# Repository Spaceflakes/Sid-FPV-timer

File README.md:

# Sid-FPV-timer

An integrated, multi node FPV drone race timing and lap tracking system designed for competitive event management and RotorHazard compatibility.

---

## Overview

**Sid-FPV-timer** is an all in one hardware timing platform engineered for competitive FPV drone racing. By integrating multi channel RF receivers, dedicated timing control, robust power regulation, and host compute docking onto a single unified board, it simplifies trackside setup and eliminates complex external wiring harnesses.

---

## Highlights

- **Multi-Node RF Tracking:** Onboard receiver array designed for multi pilot simultaneous race tracking and real time signal analysis.
- **Host Compute Docking:** Direct interface for an onboard single board computer running race timing management software.
- **Dedicated Timing Architecture:** Dedicated microcontrollers handling high-resolution lap detection, wireless connectivity, and telemetry.
- **Wide-Input Power Regulation:** High efficiency power delivery and protection circuitry designed for field battery operation.
- **Peripherals & Thermal Management:** Headers and drivers for active cooling fans, audio/visual cues, and user inputs.

---

## Inspiration & Acknowledgements

This project draws strong inspiration from the pioneering work of **[NuclearQuads](https://nuclearquads.com)** and their **NuclearHazard** timer series. Made for the open-source [RotorHazard](https://github.com/RotorHazard/RotorHazard) ecosystem.

---

## Project Structure

```text
Sid-FPV-timer/
├── PCB/                     # KiCad hardware design files
│   ├── production/          # Ready to order Gerber archives and SMT files
│   └── ...                  # Schematic sheets, board layout, and libraries
├── img/                     # 3D hardware renders & media assets
├── LICENSE                  # GNU AGPL-3.0
└── README.md
```

---

## Status

> This project is currently in active hardware prototyping and validation. Detailed documentation, firmware setups, and assembly instructions will be expanded as revisions progress.

---

## Designer

- **Designer:** Siddesh Jain ([Hex Aerospace](https://hexaerospace.in))

---

## License

This project is licensed under the **GNU Affero General Public License v3.0 (AGPL-3.0)**. See the [LICENSE](LICENSE) file for details.

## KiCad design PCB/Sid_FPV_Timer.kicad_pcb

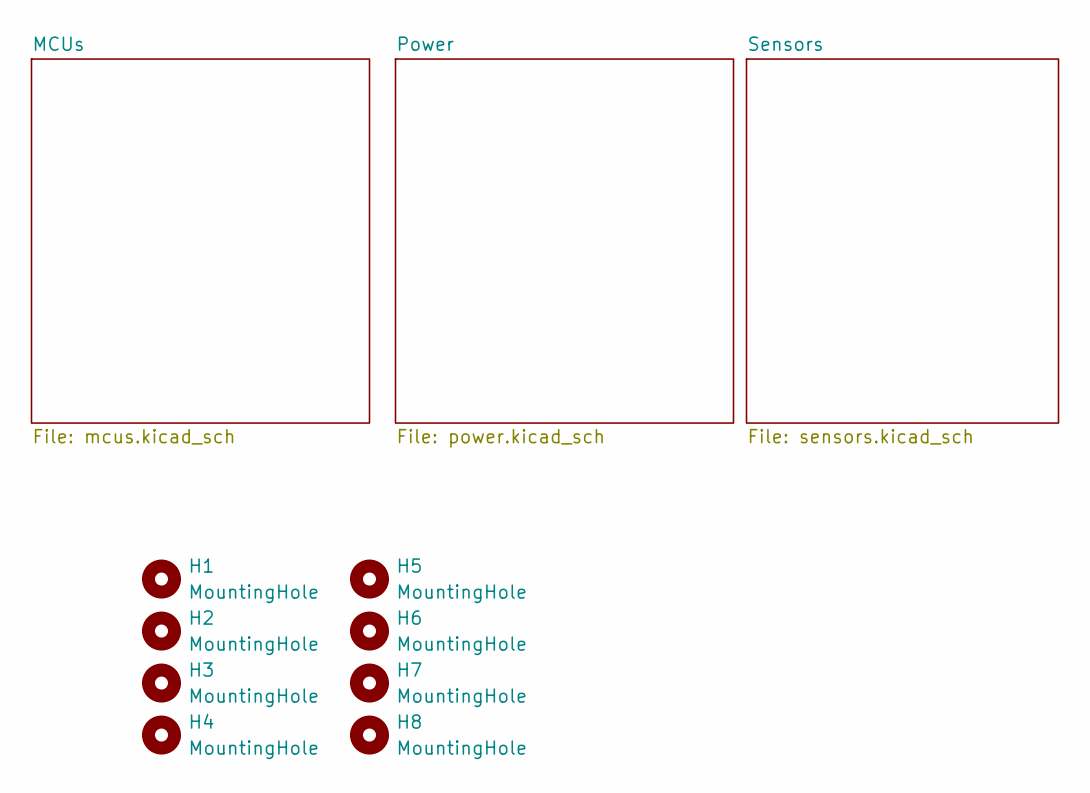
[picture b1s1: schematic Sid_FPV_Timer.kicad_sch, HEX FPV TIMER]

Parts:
H1, H2, H3, H4: MountingHole; MountingHole_2.7mm_M2.5_Pad_Via
H5, H6, H7, H8: MountingHole; MountingHole_3.2mm_M3_Pad_Via

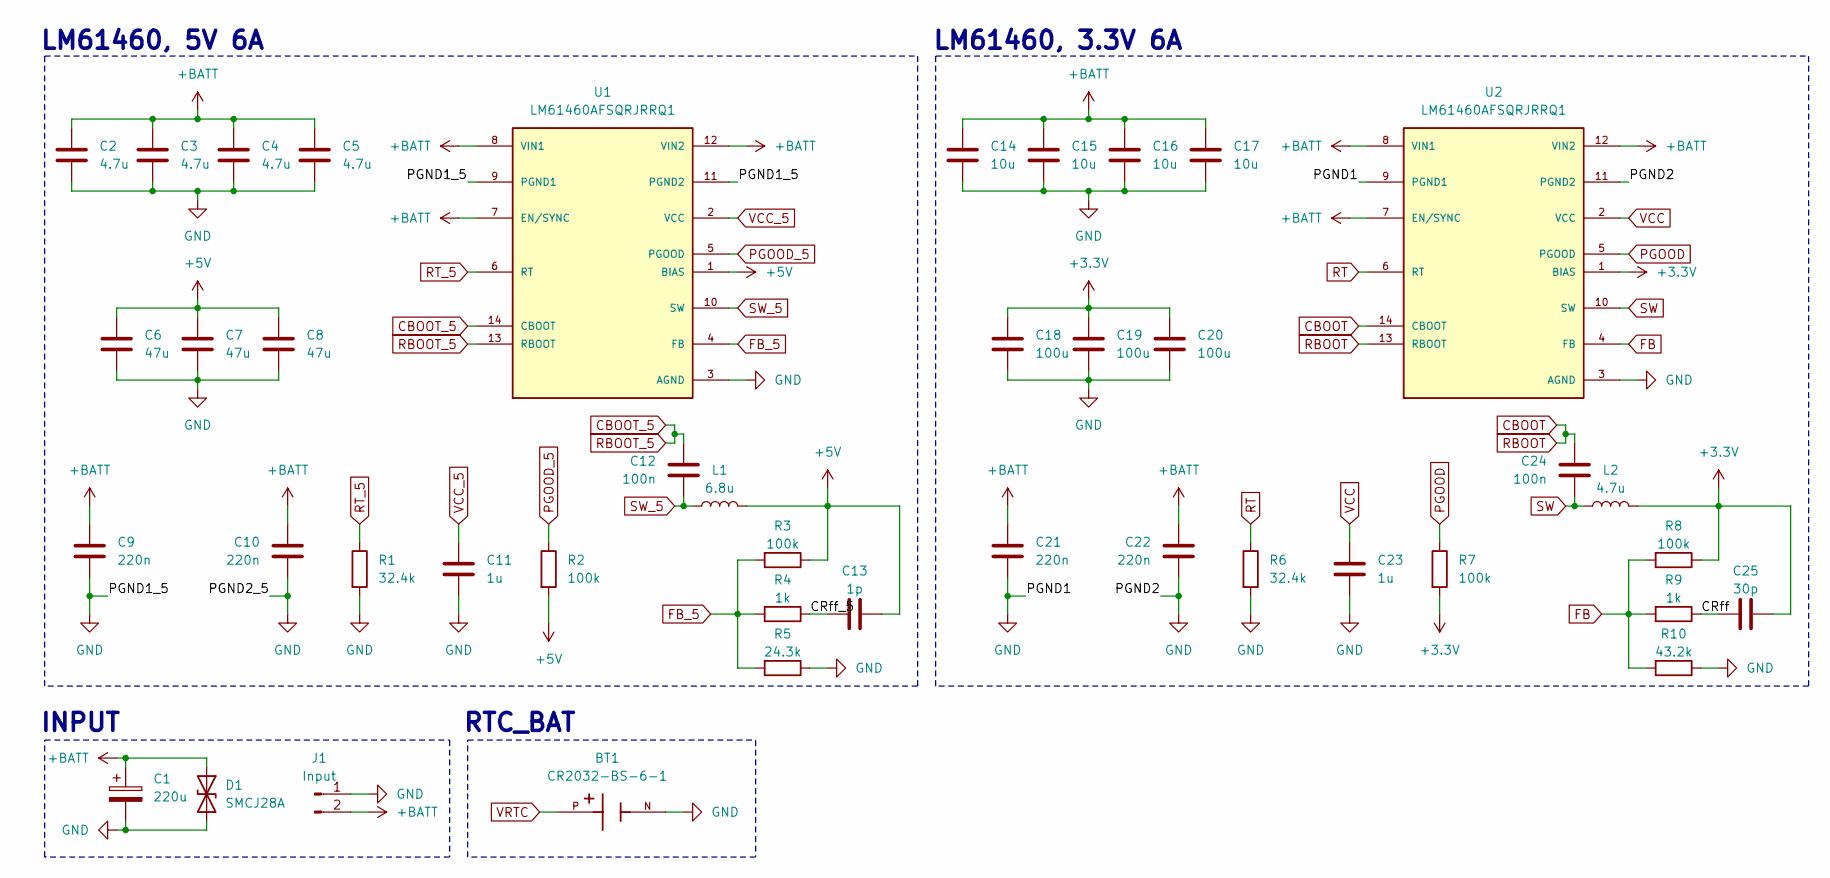
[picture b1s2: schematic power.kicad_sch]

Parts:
BT1: CR2032-BS-6-1; BatteryHolder_Keystone_1060_1x2032; MPN CR2032-BS-6-1; LCSC C964758
C1: 220u; CP_Elec_10x10; LCSC C2887271
C2, C3, C4, C5: 4.7u; C_0805_2012Metric; LCSC C98192
C6, C7, C8: 47u; C_0603_1608Metric; LCSC C730416
C9, C10, C21, C22: 220n; C_0603_1608Metric; LCSC C64705
C11, C23: 1u; C_0603_1608Metric; LCSC C15849
C12, C24: 100n; C_0603_1608Metric; LCSC C1591
C13: 1p; C_0603_1608Metric; LCSC C5137611
C14, C15, C16, C17: 10u; C_0805_2012Metric; LCSC C440198
C18, C19, C20: 100u; C_0805_2012Metric; LCSC C141660
C25: 30p; C_0603_1608Metric; LCSC C113797
D1: SMCJ28A; D_SMC; LCSC C42371538
J1: Input; AMASS_XT60PW-M_1x02_P7.20mm_Horizontal; LCSC C98732
L1: 6.8u; L_7.3x7.3_H3.5; LCSC C41415571
L2: 4.7u; L_7.3x7.3_H3.5; LCSC C167220
R1, R6: 32.4k; R_0603_1608Metric; LCSC C2982943
R2, R3, R7, R8: 100k; R_0603_1608Metric; LCSC C122538
R4, R9: 1k; R_0603_1608Metric; LCSC C118155
R5: 24.3k; R_0603_1608Metric; LCSC C403097
R10: 43.2k; R_0603_1608Metric; LCSC C2930102
U1, U2: LM61460AFSQRJRRQ1; IC_LM61460AFSQRJRRQ1; PARTREV D; LCSC C2864505

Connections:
+5V: C6.1, C7.1, C8.1, C13.2, L1.2, R2.2, R3.1, U1.1 (BIAS); also elsewhere on the board
+BATT: C1.1, C2.1, C3.1, C4.1, C5.1, C9.1, C10.1, C14.1, C15.1, C16.1, C17.1, C21.1, C22.1, D1.1 (A1), J1.2, U1.7 (EN/SYNC), U1.8 (VIN1), U1.12 (VIN2), U2.7 (EN/SYNC), U2.8 (VIN1), U2.12 (VIN2); also elsewhere on the board
/Power/CRff: C25.1, R9.1
/Power/CRff_5: C13.1, R4.1
CBOOT: C24.2, U2.13 (RBOOT), U2.14 (CBOOT)
CBOOT_5: C12.2, U1.13 (RBOOT), U1.14 (CBOOT)
FB: R8.2, R9.2, R10.2, U2.4 (FB)
FB_5: R3.2, R4.2, R5.2, U1.4 (FB)
GND: BT1.N, C1.2, C2.2, C3.2, C4.2, C5.2, C6.2, C7.2, C8.2, C9.2, C10.2, C11.2, C14.2, C15.2, C16.2, C17.2, C18.2, C19.2, C20.2, C21.2, C22.2, C23.2, D1.2 (A2), J1.1, R1.2, R5.1, R6.2, R10.1, U1.3 (AGND), U1.9 (PGND1), U1.11 (PGND2), U2.3 (AGND), U2.9 (PGND1), U2.11 (PGND2); also elsewhere on the board
PGOOD: R7.1, U2.5 (PGOOD)
PGOOD_5: R2.1, U1.5 (PGOOD)
RT: R6.1, U2.6 (RT)
RT_5: R1.1, U1.6 (RT)
SW: C24.1, L2.1, U2.10 (SW)
SW_5: C12.1, L1.1, U1.10 (SW)
VCC: C23.1, U2.2 (VCC)
VCC_5: C11.1, U1.2 (VCC)
VDD: C18.1, C19.1, C20.1, C25.2, L2.2, R7.2, R8.1, U2.1 (BIAS); also elsewhere on the board
VRTC: BT1.P; also elsewhere on the board

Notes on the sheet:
LM61460, 5V 6A
LM61460, 3.3V 6A
RTC_BAT
INPUT

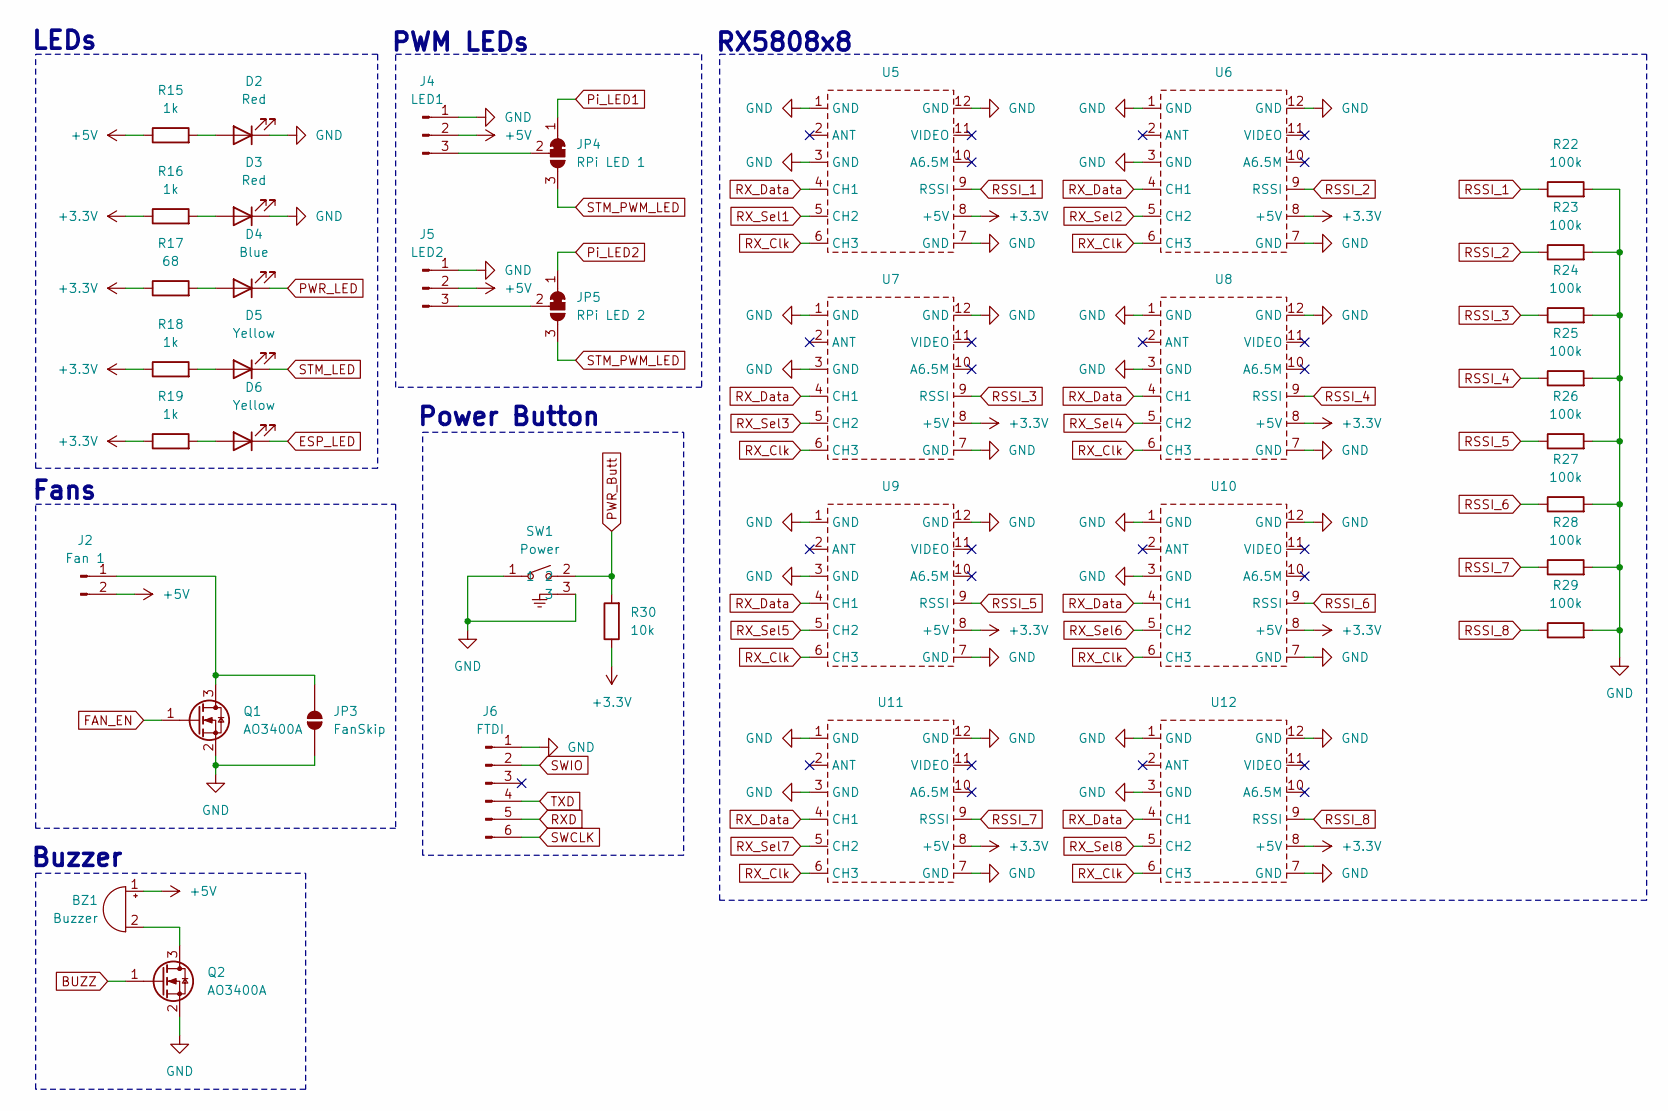
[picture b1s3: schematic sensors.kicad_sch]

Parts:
BZ1: Buzzer; Buzzer 9650Y; LCSC C96127
D2, D3: Red; LED_0805_2012Metric; LCSC C965812
D4: Blue; LED_0603_1608Metric; LCSC C46610608
D5, D6: Yellow; LED_0805_2012Metric; LCSC C965814
J2: Fan 1; JST_XA_B02B-XASK-1_1x02_P2.50mm_Vertical; LCSC C158012
J4: LED1; JST_XH_B3B-XH-A_1x03_P2.50mm_Vertical; LCSC C144394
J5: LED2; JST_XH_B3B-XH-A_1x03_P2.50mm_Vertical; LCSC C144394
J6: FTDI; PinHeader_1x06_P2.54mm_Vertical
JP3: FanSkip; SolderJumper-2_P1.3mm_Open_RoundedPad1.0x1.5mm
JP4: RPi LED 1; SolderJumper-3_P1.3mm_Bridged12_RoundedPad1.0x1.5mm
JP5: RPi LED 2; SolderJumper-3_P1.3mm_Bridged12_RoundedPad1.0x1.5mm
Q1, Q2: AO3400A; SOT-23; LCSC C20917
R15, R16, R18, R19: 1k; R_0603_1608Metric; LCSC C118155
R17: 68; R_0603_1608Metric; LCSC C27592
R22, R23, R24, R25, R26, R27, R28, R29: 100k; R_0603_1608Metric; LCSC C122538
R30: 10k; R_0603_1608Metric; LCSC C191124
SW1: Power; SW-TH_G-SWITCH_GT-TCB73B-H048-L1; LCSC C2890354
U5, U6, U7, U8, U9, U10, U11, U12: RX5808_Module

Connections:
+5V: BZ1.1 (+), J2.2, J4.2, J5.2, R15.1; also elsewhere on the board
BUZZ: Q2.1 (G); also elsewhere on the board
ESP_LED: D6.1 (K); also elsewhere on the board
FAN_EN: Q1.1 (G); also elsewhere on the board
GND: D2.1 (K), D3.1 (K), J4.1, J5.1, J6.1, JP3.1 (A), Q1.2 (S), Q2.2 (S), R22.2, R23.2, R24.2, R25.2, R26.2, R27.2, R28.2, R29.2, SW1.1, SW1.3, U5.1 (GND), U5.3 (GND), U5.7 (GND), U5.12 (GND), U6.1 (GND), U6.3 (GND), U6.7 (GND), U6.12 (GND), U7.1 (GND), U7.3 (GND), U7.7 (GND), U7.12 (GND), U8.1 (GND), U8.3 (GND), U8.7 (GND), U8.12 (GND), U9.1 (GND), U9.3 (GND), U9.7 (GND), U9.12 (GND), U10.1 (GND), U10.3 (GND), U10.7 (GND), U10.12 (GND), U11.1 (GND), U11.3 (GND), U11.7 (GND), U11.12 (GND), U12.1 (GND), U12.3 (GND), U12.7 (GND), U12.12 (GND); also elsewhere on the board
unnamed: BZ1.2 (-), Q2.3 (D)
unnamed: D2.2 (A), R15.2
unnamed: D3.2 (A), R16.2
unnamed: D4.2 (A), R17.2
unnamed: D5.2 (A), R18.2
unnamed: D6.2 (A), R19.2
unnamed: J2.1, JP3.2 (B), Q1.3 (D)
unnamed: J4.3, JP4.2 (C)
unnamed: J5.3, JP5.2 (C)
PWR_Butt: R30.2, SW1.2; also elsewhere on the board
PWR_LED: D4.1 (K); also elsewhere on the board
Pi_LED1: JP4.1 (A); also elsewhere on the board
Pi_LED2: JP5.1 (A); also elsewhere on the board
RSSI_1: R22.1, U5.9 (RSSI); also elsewhere on the board
RSSI_2: R23.1, U6.9 (RSSI); also elsewhere on the board
RSSI_3: R24.1, U7.9 (RSSI); also elsewhere on the board
RSSI_4: R25.1, U8.9 (RSSI); also elsewhere on the board
RSSI_5: R26.1, U9.9 (RSSI); also elsewhere on the board
RSSI_6: R27.1, U10.9 (RSSI); also elsewhere on the board
RSSI_7: R28.1, U11.9 (RSSI); also elsewhere on the board
RSSI_8: R29.1, U12.9 (RSSI); also elsewhere on the board
RXD: J6.5; also elsewhere on the board
RX_Clk: U5.6 (CH3), U6.6 (CH3), U7.6 (CH3), U8.6 (CH3), U9.6 (CH3), U10.6 (CH3), U11.6 (CH3), U12.6 (CH3); also elsewhere on the board
RX_Data: U5.4 (CH1), U6.4 (CH1), U7.4 (CH1), U8.4 (CH1), U9.4 (CH1), U10.4 (CH1), U11.4 (CH1), U12.4 (CH1); also elsewhere on the board
RX_Sel1: U5.5 (CH2); also elsewhere on the board
RX_Sel2: U6.5 (CH2); also elsewhere on the board
RX_Sel3: U7.5 (CH2); also elsewhere on the board
RX_Sel4: U8.5 (CH2); also elsewhere on the board
RX_Sel5: U9.5 (CH2); also elsewhere on the board
RX_Sel6: U10.5 (CH2); also elsewhere on the board
RX_Sel7: U11.5 (CH2); also elsewhere on the board
RX_Sel8: U12.5 (CH2); also elsewhere on the board
STM_LED: D5.1 (K); also elsewhere on the board
STM_PWM_LED: JP4.3 (B), JP5.3 (B); also elsewhere on the board
SWCLK: J6.6; also elsewhere on the board
SWIO: J6.2; also elsewhere on the board
TXD: J6.4; also elsewhere on the board
VDD: R16.1, R17.1, R18.1, R19.1, R30.1, U5.8 (+5V), U6.8 (+5V), U7.8 (+5V), U8.8 (+5V), U9.8 (+5V), U10.8 (+5V), U11.8 (+5V), U12.8 (+5V); also elsewhere on the board

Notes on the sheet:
Power Button
PWM LEDs
Buzzer
RX5808x8
Fans
LEDs

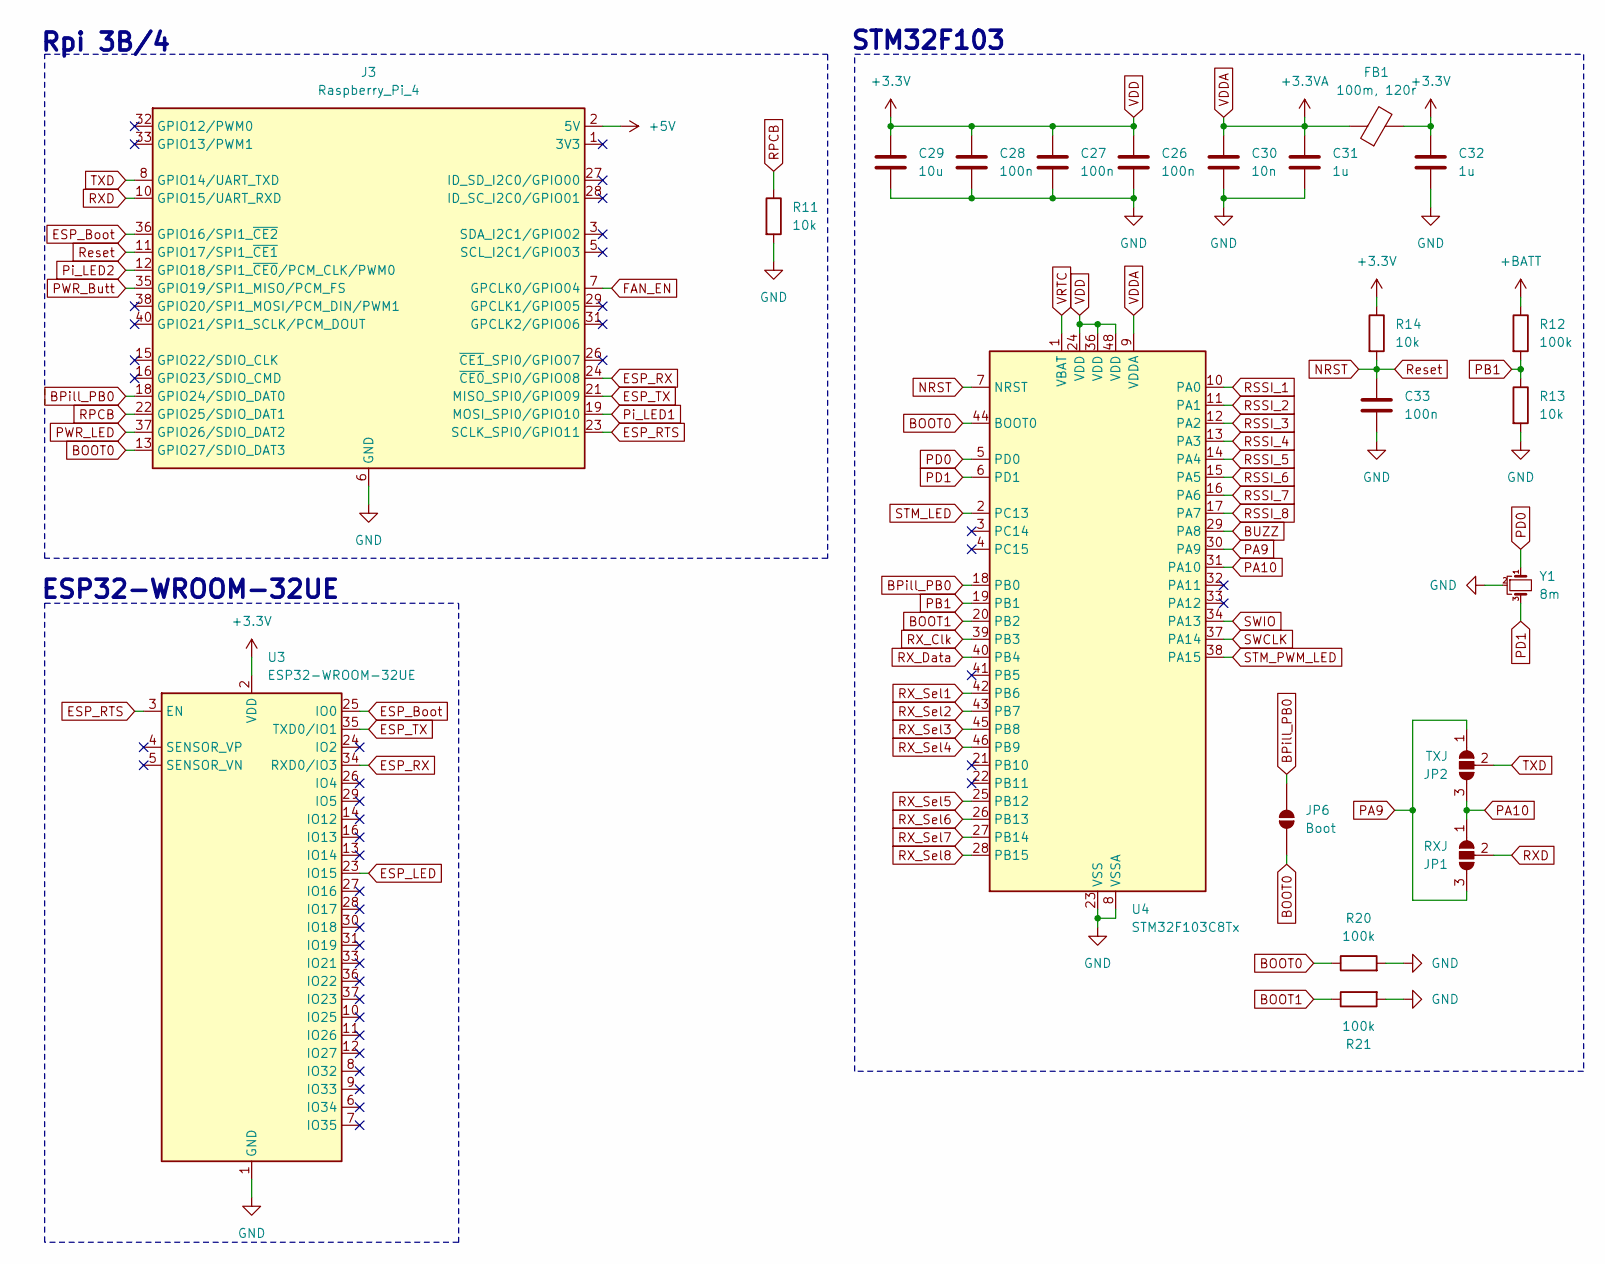
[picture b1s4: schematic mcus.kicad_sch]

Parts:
C26, C27, C28, C33: 100n; C_0603_1608Metric; LCSC C1591
C29: 10u; C_0603_1608Metric; LCSC C92487
C30: 10n; C_0603_1608Metric; LCSC C100042
C31, C32: 1u; C_0603_1608Metric; LCSC C15849
FB1: 100m, 120r; C_0603_1608Metric; LCSC C76893
J3: Raspberry_Pi_4; PinSocket_2x20_P2.54mm_Vertical; LCSC C2977589
JP1: RXJ; SolderJumper-3_P1.3mm_Open_RoundedPad1.0x1.5mm_NumberLabels
JP2: TXJ; SolderJumper-3_P1.3mm_Open_RoundedPad1.0x1.5mm_NumberLabels
JP6: Boot; SolderJumper-2_P1.3mm_Open_RoundedPad1.0x1.5mm
R11, R13, R14: 10k; R_0603_1608Metric; LCSC C191124
R12, R20, R21: 100k; R_0603_1608Metric; LCSC C122538
U3: ESP32-WROOM-32UE; LCSC C701346
U4: STM32F103C8Tx; LQFP-48_7x7mm_P0.5mm; LCSC C8734
Y1: 8m; Resonator_SMD_Murata_CSTxExxV-3Pin_3.0x1.1mm; LCSC C22549

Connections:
+5V: J3.2 (5V), J3.4 (5V); also elsewhere on the board
+BATT: R12.1; also elsewhere on the board
BOOT0: J3.13 (GPIO27/SDIO_DAT3), JP6.1 (A), R20.1, U4.44 (BOOT0)
BOOT1: R21.1, U4.20 (PB2)
BPill_PB0: J3.18 (GPIO24/SDIO_DAT0), JP6.2 (B), U4.18 (PB0)
BUZZ: U4.29 (PA8); also elsewhere on the board
ESP_Boot: J3.36 (GPIO16/SPI1_~CE2), U3.25 (IO0)
ESP_LED: U3.23 (IO15); also elsewhere on the board
ESP_RTS: J3.23 (SCLK_SPI0/GPIO11), U3.3 (EN)
ESP_RX: J3.24 (~CE0_SPI0/GPIO08), U3.34 (RXD0/IO3)
ESP_TX: J3.21 (MISO_SPI0/GPIO09), U3.35 (TXD0/IO1)
FAN_EN: J3.7 (GPCLK0/GPIO04); also elsewhere on the board
GND: C26.2, C27.2, C28.2, C29.2, C30.2, C31.2, C32.2, C33.2, J3.6 (GND), J3.9 (GND), J3.14 (GND), J3.20 (GND), J3.25 (GND), J3.30 (GND), J3.34 (GND), J3.39 (GND), R11.2, R13.2, R20.2, R21.2, U3.1 (GND), U3.15 (GND), U3.38 (GND), U3.39 (GND), U4.8 (VSSA), U4.23 (VSS), U4.35 (VSS), U4.47 (VSS), Y1.2; also elsewhere on the board
NRST: C33.1, J3.11 (GPIO17/SPI1_~CE1), R14.2, U4.7 (NRST)
PA9: JP1.3 (B), JP2.1 (A), U4.30 (PA9)
PA10: JP1.1 (A), JP2.3 (B), U4.31 (PA10)
PB1: R12.2, R13.1, U4.19 (PB1)
PD0: U4.5 (PD0), Y1.1
PD1: U4.6 (PD1), Y1.3
PWR_Butt: J3.35 (GPIO19/SPI1_MISO/PCM_FS); also elsewhere on the board
PWR_LED: J3.37 (GPIO26/SDIO_DAT2); also elsewhere on the board
Pi_LED1: J3.19 (MOSI_SPI0/GPIO10); also elsewhere on the board
Pi_LED2: J3.12 (GPIO18/SPI1_~CE0/PCM_CLK/PWM0); also elsewhere on the board
RPCB: J3.22 (GPIO25/SDIO_DAT1), R11.1
RSSI_1: U4.10 (PA0); also elsewhere on the board
RSSI_2: U4.11 (PA1); also elsewhere on the board
RSSI_3: U4.12 (PA2); also elsewhere on the board
RSSI_4: U4.13 (PA3); also elsewhere on the board
RSSI_5: U4.14 (PA4); also elsewhere on the board
RSSI_6: U4.15 (PA5); also elsewhere on the board
RSSI_7: U4.16 (PA6); also elsewhere on the board
RSSI_8: U4.17 (PA7); also elsewhere on the board
RXD: J3.10 (GPIO15/UART_RXD), JP1.2 (C); also elsewhere on the board
RX_Clk: U4.39 (PB3); also elsewhere on the board
RX_Data: U4.40 (PB4); also elsewhere on the board
RX_Sel1: U4.42 (PB6); also elsewhere on the board
RX_Sel2: U4.43 (PB7); also elsewhere on the board
RX_Sel3: U4.45 (PB8); also elsewhere on the board
RX_Sel4: U4.46 (PB9); also elsewhere on the board
RX_Sel5: U4.25 (PB12); also elsewhere on the board
RX_Sel6: U4.26 (PB13); also elsewhere on the board
RX_Sel7: U4.27 (PB14); also elsewhere on the board
RX_Sel8: U4.28 (PB15); also elsewhere on the board
STM_LED: U4.2 (PC13); also elsewhere on the board
STM_PWM_LED: U4.38 (PA15); also elsewhere on the board
SWCLK: U4.37 (PA14); also elsewhere on the board
SWIO: U4.34 (PA13); also elsewhere on the board
TXD: J3.8 (GPIO14/UART_TXD), JP2.2 (C); also elsewhere on the board
VDD: C26.1, C27.1, C28.1, C29.1, C32.1, FB1.2, R14.1, U3.2 (VDD), U4.24 (VDD), U4.36 (VDD), U4.48 (VDD); also elsewhere on the board
VDDA: C30.1, C31.1, FB1.1, U4.9 (VDDA)
VRTC: U4.1 (VBAT); also elsewhere on the board

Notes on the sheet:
ESP32-WROOM-32UE
Rpi 3B/4
STM32F103

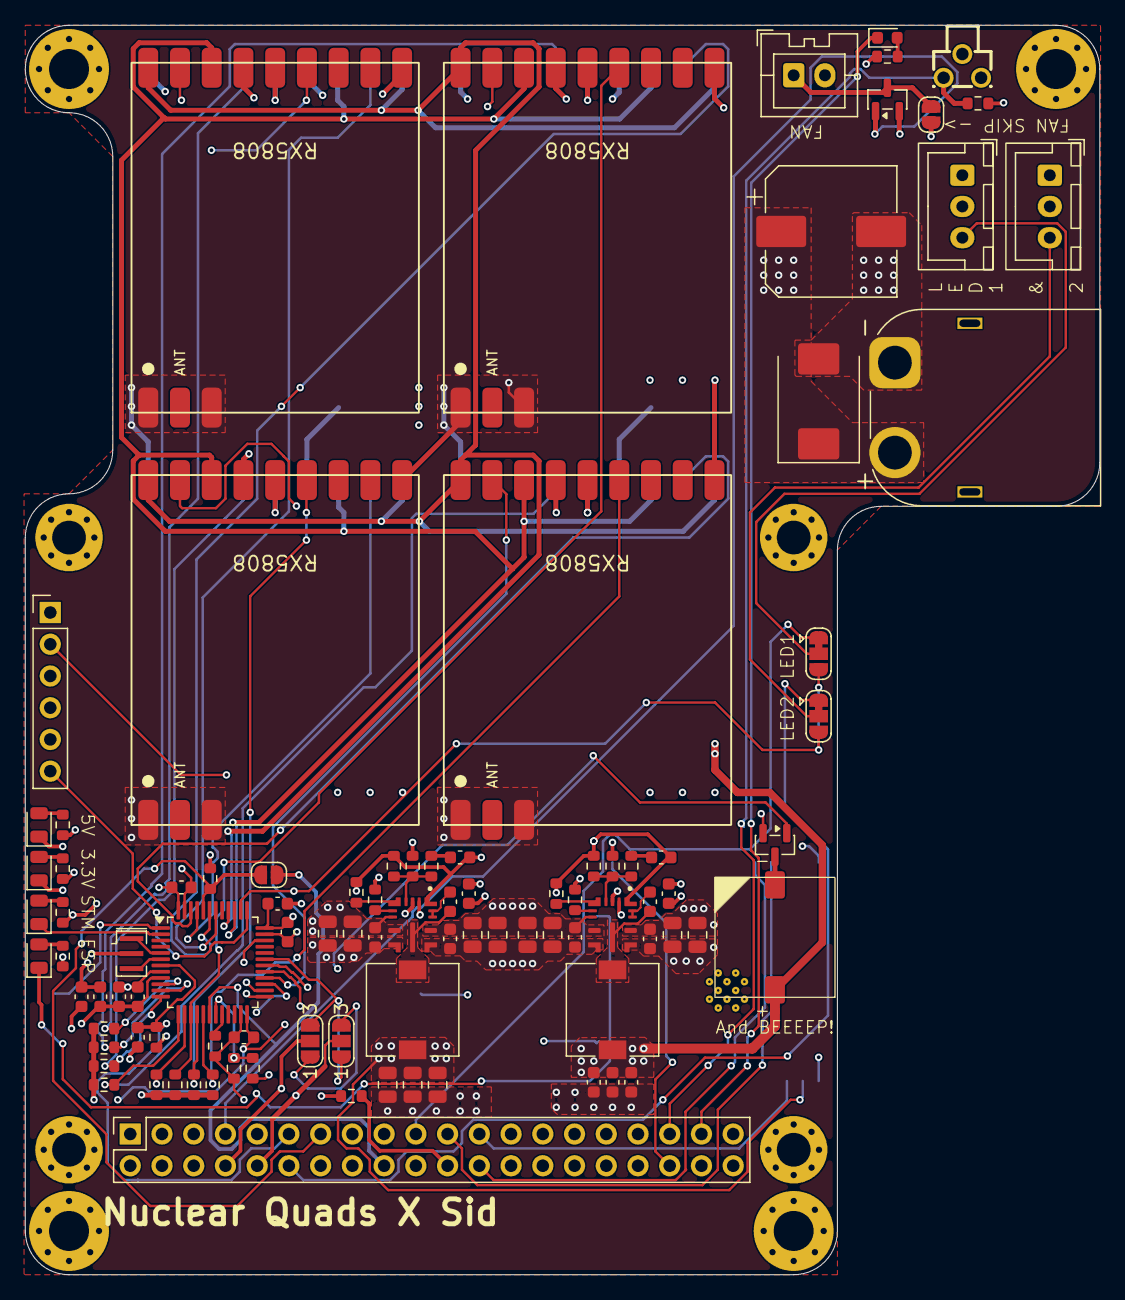
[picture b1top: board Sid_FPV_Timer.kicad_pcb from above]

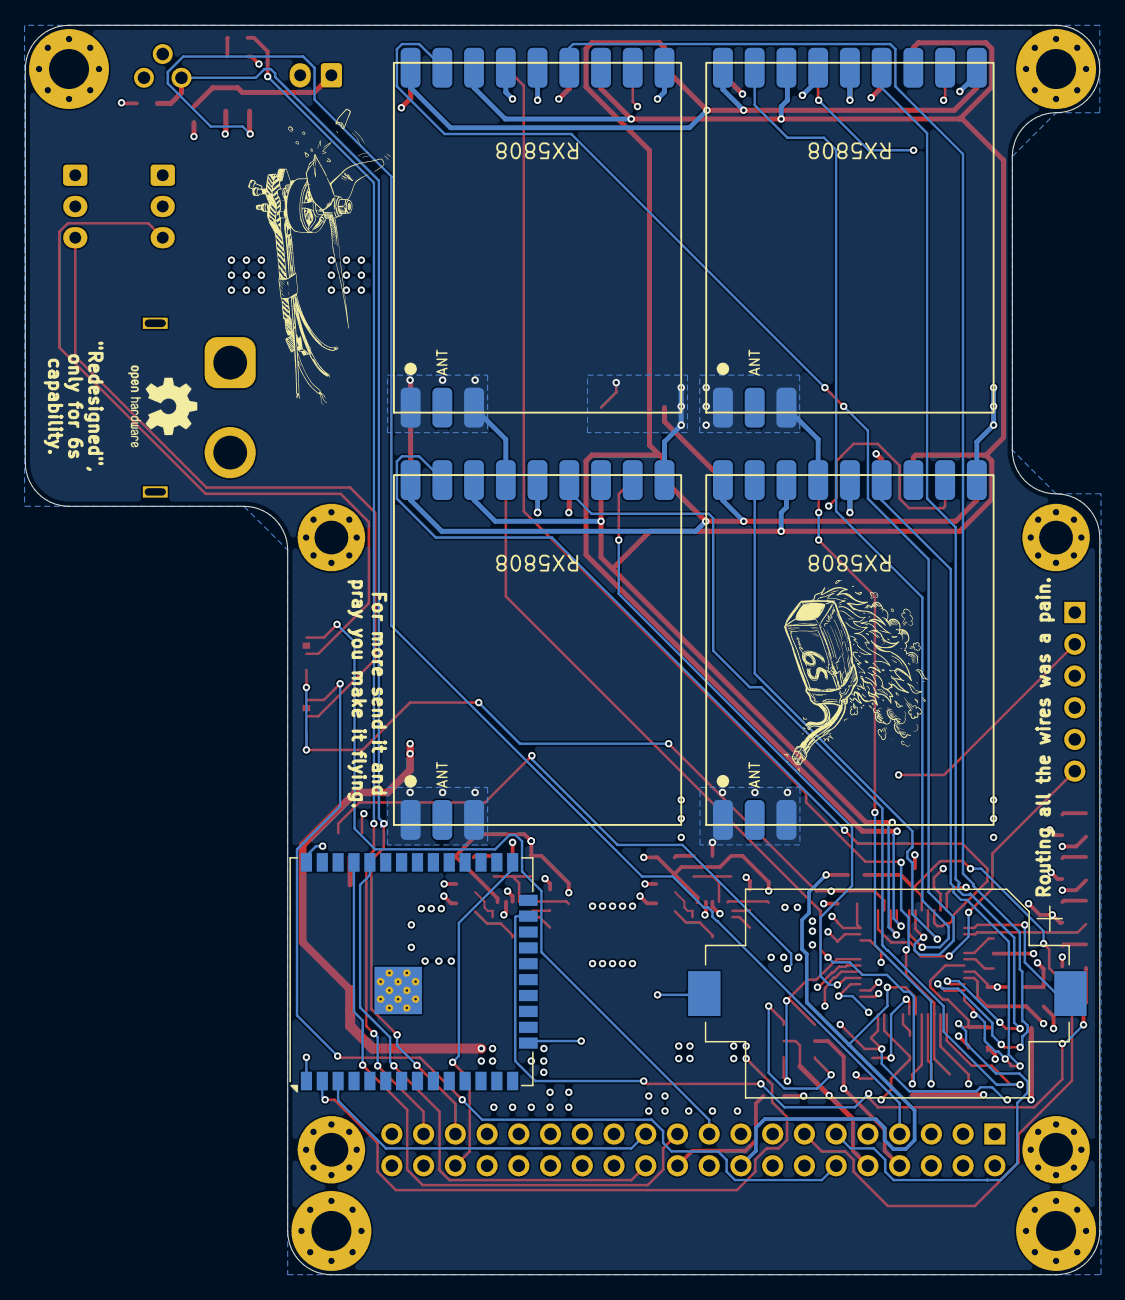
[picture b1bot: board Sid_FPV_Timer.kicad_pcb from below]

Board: 4 copper layers, 86.0 x 100.0 mm, 110 parts (6 on the bottom side), 74 nets.

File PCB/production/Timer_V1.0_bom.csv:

Designator,Footprint,Quantity,Value,LCSC Part #
BT1,BatteryHolder_Keystone_1060_1x2032,1,CR2032-BS-6-1,C964758
BZ1,Buzzer 9650Y,1,Buzzer,C96127
C1,CP_Elec_10x10,1,220u,C2887271
"C10, C21, C22, C9",0603,4,220n,C64705
"C11, C23, C31, C32",0603,4,1u,C15849
"C12, C24, C26, C27, C28, C33",0603,6,100n,C1591
C13,0603,1,1p,C5137611
"C14, C15, C16, C17",0805,4,10u,C440198
"C18, C19, C20",0805,3,100u,C141660
"C2, C3, C4, C5",0805,4,4.7u,C98192
C25,0603,1,30p,C113797
C29,0603,1,10u,C92487
C30,0603,1,10n,C100042
"C6, C7, C8",0603,3,47u,C730416
D1,D_SMC,1,SMCJ28A,C42371538
"D2, D3",0805,2,Red,C965812
D4,0603,1,Blue,C46610608
"D5, D6",0805,2,Yellow,C965814
FB1,0603,1,"100m, 120r",C76893
J1,AMASS_XT60PW-M_1x02_P7.20mm_Horizontal,1,Input,C98732
J2,JST_XA_B02B-XASK-1_1x02_P2.50mm_Vertical,1,Fan 1,C158012
J3,PinSocket_2x20_P2.54mm_Vertical,1,Raspberry_Pi_4,C2977589
J4,JST_XH_B3B-XH-A_1x03_P2.50mm_Vertical,1,LED1,C144394
J5,JST_XH_B3B-XH-A_1x03_P2.50mm_Vertical,1,LED2,C144394
L1,L_7.3x7.3_H3.5,1,6.8u,C41415571
L2,L_7.3x7.3_H3.5,1,4.7u,C167220
"Q1, Q2",SOT-23,2,AO3400A,C20917
"R1, R6",0603,2,32.4k,C2982943
R10,0603,1,43.2k,C2930102
"R11, R13, R14, R30",0603,4,10k,C191124
"R12, R2, R20, R21, R22, R23, R24, R25, R26, R27, R28, R29, R3, R7, R8",0603,15,100k,C122538
"R15, R16, R18, R19, R4, R9",0603,6,1k,C118155
R17,0603,1,68,C27592
R5,0603,1,24.3k,C403097
SW1,SW-TH_G-SWITCH_GT-TCB73B-H048-L1,1,Power,C2890354
"U1, U2",IC_LM61460AFSQRJRRQ1,2,LM61460AFSQRJRRQ1,C2864505
U4,LQFP-48_7x7mm_P0.5mm,1,STM32F103C8Tx,C8734
Y1,Resonator_SMD_Murata_CSTxExxV-3Pin_3.0x1.1mm,1,8m,C22549
